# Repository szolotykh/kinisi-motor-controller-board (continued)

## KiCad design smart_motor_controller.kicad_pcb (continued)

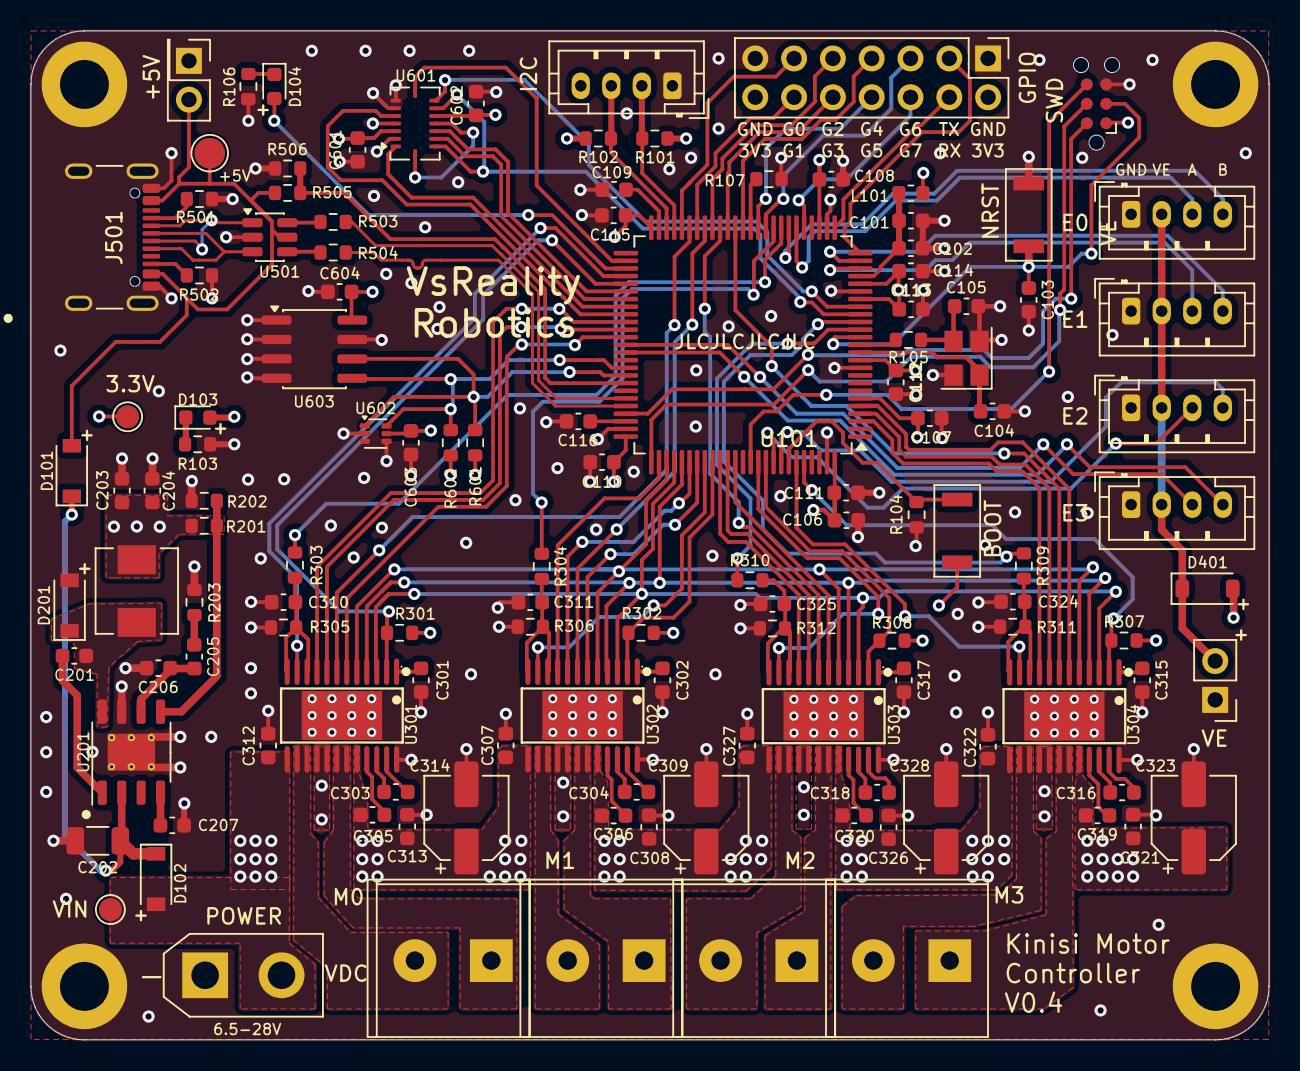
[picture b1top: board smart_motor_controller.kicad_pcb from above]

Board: 4 copper layers, 81.0 x 66.0 mm, 128 parts (0 on the bottom side), 125 nets.

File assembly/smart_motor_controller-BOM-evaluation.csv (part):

"Reference","Value","Footprint","LCSC Part #","Part Evaluation"
"C101","1u","Capacitor_SMD:C_0603_1608Metric","C15849","OK: Samsung CL10A105KB8NNNC, 1uF 50V X5R 0603 - value and package match the schematic symbol and the PCB land pattern."
"C102","10nf","Capacitor_SMD:C_0603_1608Metric","C57112","OK: FH 0603B103K500NT, 10nF 50V X7R 0603 - value and package match the schematic symbol and the PCB land pattern."
"C103","1u","Capacitor_SMD:C_0603_1608Metric","C15849","OK: Samsung CL10A105KB8NNNC, 1uF 50V X5R 0603 - value and package match the schematic symbol and the PCB land pattern."
"C104","12p","Capacitor_SMD:C_0603_1608Metric","C1642","OK: FH 0603CG120J500NT, 12pF 50V C0G 0603 - C0G dielectric is correct for crystal load caps; 12pF pair with ~3pF stray gives the 9pF CL the crystal wants."
"C105","12p","Capacitor_SMD:C_0603_1608Metric","C1642","OK: FH 0603CG120J500NT, 12pF 50V C0G 0603 - C0G dielectric is correct for crystal load caps; 12pF pair with ~3pF stray gives the 9pF CL the crystal wants."
"C106","4u7","Capacitor_SMD:C_0603_1608Metric","C19666","OK: Samsung CL10A475KO8NNNC, 4.7uF 16V X5R 0603 - value and package match the schematic symbol and the PCB land pattern."
"C107","100nf","Capacitor_SMD:C_0603_1608Metric","C694249","OK: FH 0603B104K250NT, 100nF 25V X7R 0603 - value and package match the schematic symbol and the PCB land pattern."
"C108","100nf","Capacitor_SMD:C_0603_1608Metric","C694249","OK: FH 0603B104K250NT, 100nF 25V X7R 0603 - value and package match the schematic symbol and the PCB land pattern."
"C109","100nf","Capacitor_SMD:C_0603_1608Metric","C694249","OK: FH 0603B104K250NT, 100nF 25V X7R 0603 - value and package match the schematic symbol and the PCB land pattern."
"C110","100nf","Capacitor_SMD:C_0603_1608Metric","C694249","OK: FH 0603B104K250NT, 100nF 25V X7R 0603 - value and package match the schematic symbol and the PCB land pattern."
"C111","100nf","Capacitor_SMD:C_0603_1608Metric","C694249","OK: FH 0603B104K250NT, 100nF 25V X7R 0603 - value and package match the schematic symbol and the PCB land pattern."
"C112","100nf","Capacitor_SMD:C_0603_1608Metric","C694249","OK: FH 0603B104K250NT, 100nF 25V X7R 0603 - value and package match the schematic symbol and the PCB land pattern."
"C113","100nf","Capacitor_SMD:C_0603_1608Metric","C694249","OK: FH 0603B104K250NT, 100nF 25V X7R 0603 - value and package match the schematic symbol and the PCB land pattern."
"C114","100nf","Capacitor_SMD:C_0603_1608Metric","C694249","OK: FH 0603B104K250NT, 100nF 25V X7R 0603 - value and package match the schematic symbol and the PCB land pattern."
"C115","2.2u","Capacitor_SMD:C_0603_1608Metric","C23630","OK: Samsung CL10A225KO8NNNC, 2.2uF 16V X5R 0603 - value and package match the schematic symbol and the PCB land pattern."
"C116","2.2u","Capacitor_SMD:C_0603_1608Metric","C23630","OK: Samsung CL10A225KO8NNNC, 2.2uF 16V X5R 0603 - value and package match the schematic symbol and the PCB land pattern."
"C201","100nf","Capacitor_SMD:C_0603_1608Metric","C694249","OK: FH 0603B104K250NT, 100nF 25V X7R 0603 - value and package match the schematic symbol and the PCB land pattern."
"C202","10uf","Capacitor_SMD:C_1206_3216Metric","C13585","OK: Samsung CL31A106KBHNNNE, 10uF 50V X5R 1206 - value and package match the schematic symbol and the PCB land pattern."
"C203","47uF","Capacitor_SMD:C_0603_1608Metric","C140782","OK WITH CAUTION: Murata GRM188R60J476ME15D, 47uF 6.3V X5R 0603 - on the +3V3 buck output; 6.3V rating is only 2x the 3.3V rail and X5R DC-bias derating at 3.3V leaves roughly a third of nominal capacitance. Functionally adequate in parallel, but the least-margin part in the BOM."
"C204","47uF","Capacitor_SMD:C_0603_1608Metric","C140782","OK WITH CAUTION: Murata GRM188R60J476ME15D, 47uF 6.3V X5R 0603 - on the +3V3 buck output; 6.3V rating is only 2x the 3.3V rail and X5R DC-bias derating at 3.3V leaves roughly a third of nominal capacitance. Functionally adequate in parallel, but the least-margin part in the BOM."
"C205","1nF","Capacitor_SMD:C_0603_1608Metric","C340644","OK: Walsin 0603N102J500CT, 1nF 50V NP0 0603 - value and package match the schematic symbol and the PCB land pattern."
"C206","10nf","Capacitor_SMD:C_0603_1608Metric","C57112","OK: FH 0603B103K500NT, 10nF 50V X7R 0603 - value and package match the schematic symbol and the PCB land pattern."
"C207","8.2nF","Capacitor_SMD:C_0603_1608Metric","C1322360","OK: FH 0603B822K500NT, 8.2nF 50V X7R 0603 - value and package match the schematic symbol and the PCB land pattern."
"C301","1u","Capacitor_SMD:C_0603_1608Metric","C90540","OK: FH 0603B105K500NT, 1uF 50V X7R 0603 - value and package match the schematic symbol and the PCB land pattern."
"C302","1u","Capacitor_SMD:C_0603_1608Metric","C90540","OK: FH 0603B105K500NT, 1uF 50V X7R 0603 - value and package match the schematic symbol and the PCB land pattern."
"C303","47n","Capacitor_SMD:C_0603_1608Metric","C696860","OK - SUPPLY RISK: CCTC TCC0603X7R473M500CT, 47nF 50V X7R 0603 - correct value/package, but LCSC stock was about 400 pcs at time of check and four are needed per board. Drop-in alternate: C1622 (Samsung CL10B473KB8NNNC, same 47nF 50V X7R 0603)."
"C304","47n","Capacitor_SMD:C_0603_1608Metric","C696860","OK - SUPPLY RISK: CCTC TCC0603X7R473M500CT, 47nF 50V X7R 0603 - correct value/package, but LCSC stock was about 400 pcs at time of check and four are needed per board. Drop-in alternate: C1622 (Samsung CL10B473KB8NNNC, same 47nF 50V X7R 0603)."
"C305","1u","Capacitor_SMD:C_0603_1608Metric","C90540","OK: FH 0603B105K500NT, 1uF 50V X7R 0603 - value and package match the schematic symbol and the PCB land pattern."
"C306","1u","Capacitor_SMD:C_0603_1608Metric","C90540","OK: FH 0603B105K500NT, 1uF 50V X7R 0603 - value and package match the schematic symbol and the PCB land pattern."
"C307","100n","Capacitor_SMD:C_0603_1608Metric","C14663","OK: Yageo CC0603KRX7R9BB104, 100nF 50V X7R 0603 - value and package match the schematic symbol and the PCB land pattern."
"C308","100n","Capacitor_SMD:C_0603_1608Metric","C14663","OK: Yageo CC0603KRX7R9BB104, 100nF 50V X7R 0603 - value and package match the schematic symbol and the PCB land pattern."
"C309","47u","Capacitor_THT:CP_Radial_D5.0mm_P2.00mm","C22387982","OK - FOOTPRINT FIELD STALE: FOLLON EFVM035ADA470M0554, 47uF 35V SMD D5xL5.4mm - part matches the PCB land pattern CP_Elec_5x5.4, but the schematic Footprint field still reads Capacitor_THT:CP_Radial_D5.0mm_P2.00mm, so the exported BOM advertises a through-hole footprint for an SMD part."
"C310","1u","Capacitor_SMD:C_0603_1608Metric","C90540","OK: FH 0603B105K500NT, 1uF 50V X7R 0603 - value and package match the schematic symbol and the PCB land pattern."
"C311","1u","Capacitor_SMD:C_0603_1608Metric","C90540","OK: FH 0603B105K500NT, 1uF 50V X7R 0603 - value and package match the schematic symbol and the PCB land pattern."
"C312","100n","Capacitor_SMD:C_0603_1608Metric","C14663","OK: Yageo CC0603KRX7R9BB104, 100nF 50V X7R 0603 - value and package match the schematic symbol and the PCB land pattern."
"C313","100n","Capacitor_SMD:C_0603_1608Metric","C14663","OK: Yageo CC0603KRX7R9BB104, 100nF 50V X7R 0603 - value and package match the schematic symbol and the PCB land pattern."
"C314","47u","Capacitor_THT:CP_Radial_D5.0mm_P2.00mm","C22387982","OK - FOOTPRINT FIELD STALE: FOLLON EFVM035ADA470M0554, 47uF 35V SMD D5xL5.4mm - part matches the PCB land pattern CP_Elec_5x5.4, but the schematic Footprint field still reads Capacitor_THT:CP_Radial_D5.0mm_P2.00mm, so the exported BOM advertises a through-hole footprint for an SMD part."
"C315","1u","Capacitor_SMD:C_0603_1608Metric","C90540","OK: FH 0603B105K500NT, 1uF 50V X7R 0603 - value and package match the schematic symbol and the PCB land pattern."
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
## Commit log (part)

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2021-03-14 Init
2021-03-15 Finish routing
2021-03-21 v0.1 Original design
2021-03-25 V0.1.1 Removed fuse and AO3401A
2021-03-25 Add 3d view image
2021-04-01 Add assembly and gerber files
2021-05-27 First draft
2021-06-13 Layout
2022-03-18 Additional changes
2022-03-26 Change footprint for a comonent
2022-03-26 Update manufacturing files
2022-03-29 Fixed issue with diodes
2022-06-13 Change in FDD6685
2022-06-18 Update labels on the board
2023-04-01 Initial update
2023-04-03 Edge of the bpard
2023-04-22 Change components to 0603
2023-04-23 Reorganized motor drivers
2023-04-30 Complete layout
2023-04-30 Updated image
2023-06-18 Create LICENSE
2023-08-08 Updated gedber files
2026-06-29 Add CLAUDE.md for repository guidance and design documentation
    - Introduced CLAUDE.md to provide an overview of the Kinisi smart motor controller board design.
    - Included details on editing design files, fabrication workflow for JLCPCB, and revision management.
    - Documented companion repositories for firmware and client libraries.
